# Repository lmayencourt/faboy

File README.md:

# faboy
arduboy clone for the fablab of Sion (CH)

## faboyBLE (V2)
The new version of the faboy is based on a nrf52822 module, an ARM cortex M0+ based processor with Bluetooth Smart. This will allow the possibility to change game wia BLE or UART and to have multiplayer games.  
### status

* PCB designed, ordered and mounted

### issues 
* cannot programm the nrf module...

## idea for v2 
  * NRF24l for a wireless communication
  * capacitive button
  * coin-cell battery / thin film battery 
  * different switch pattern
  * ARM processor 
  * solar cell
  * PCB usb connector 
  * battery monitoring with ADC

## issues 
  * bad usb connector (mini b instead of micro b !)
  * difficult to find a gnd test pad on the top 
  * battery operation crash after a small moment

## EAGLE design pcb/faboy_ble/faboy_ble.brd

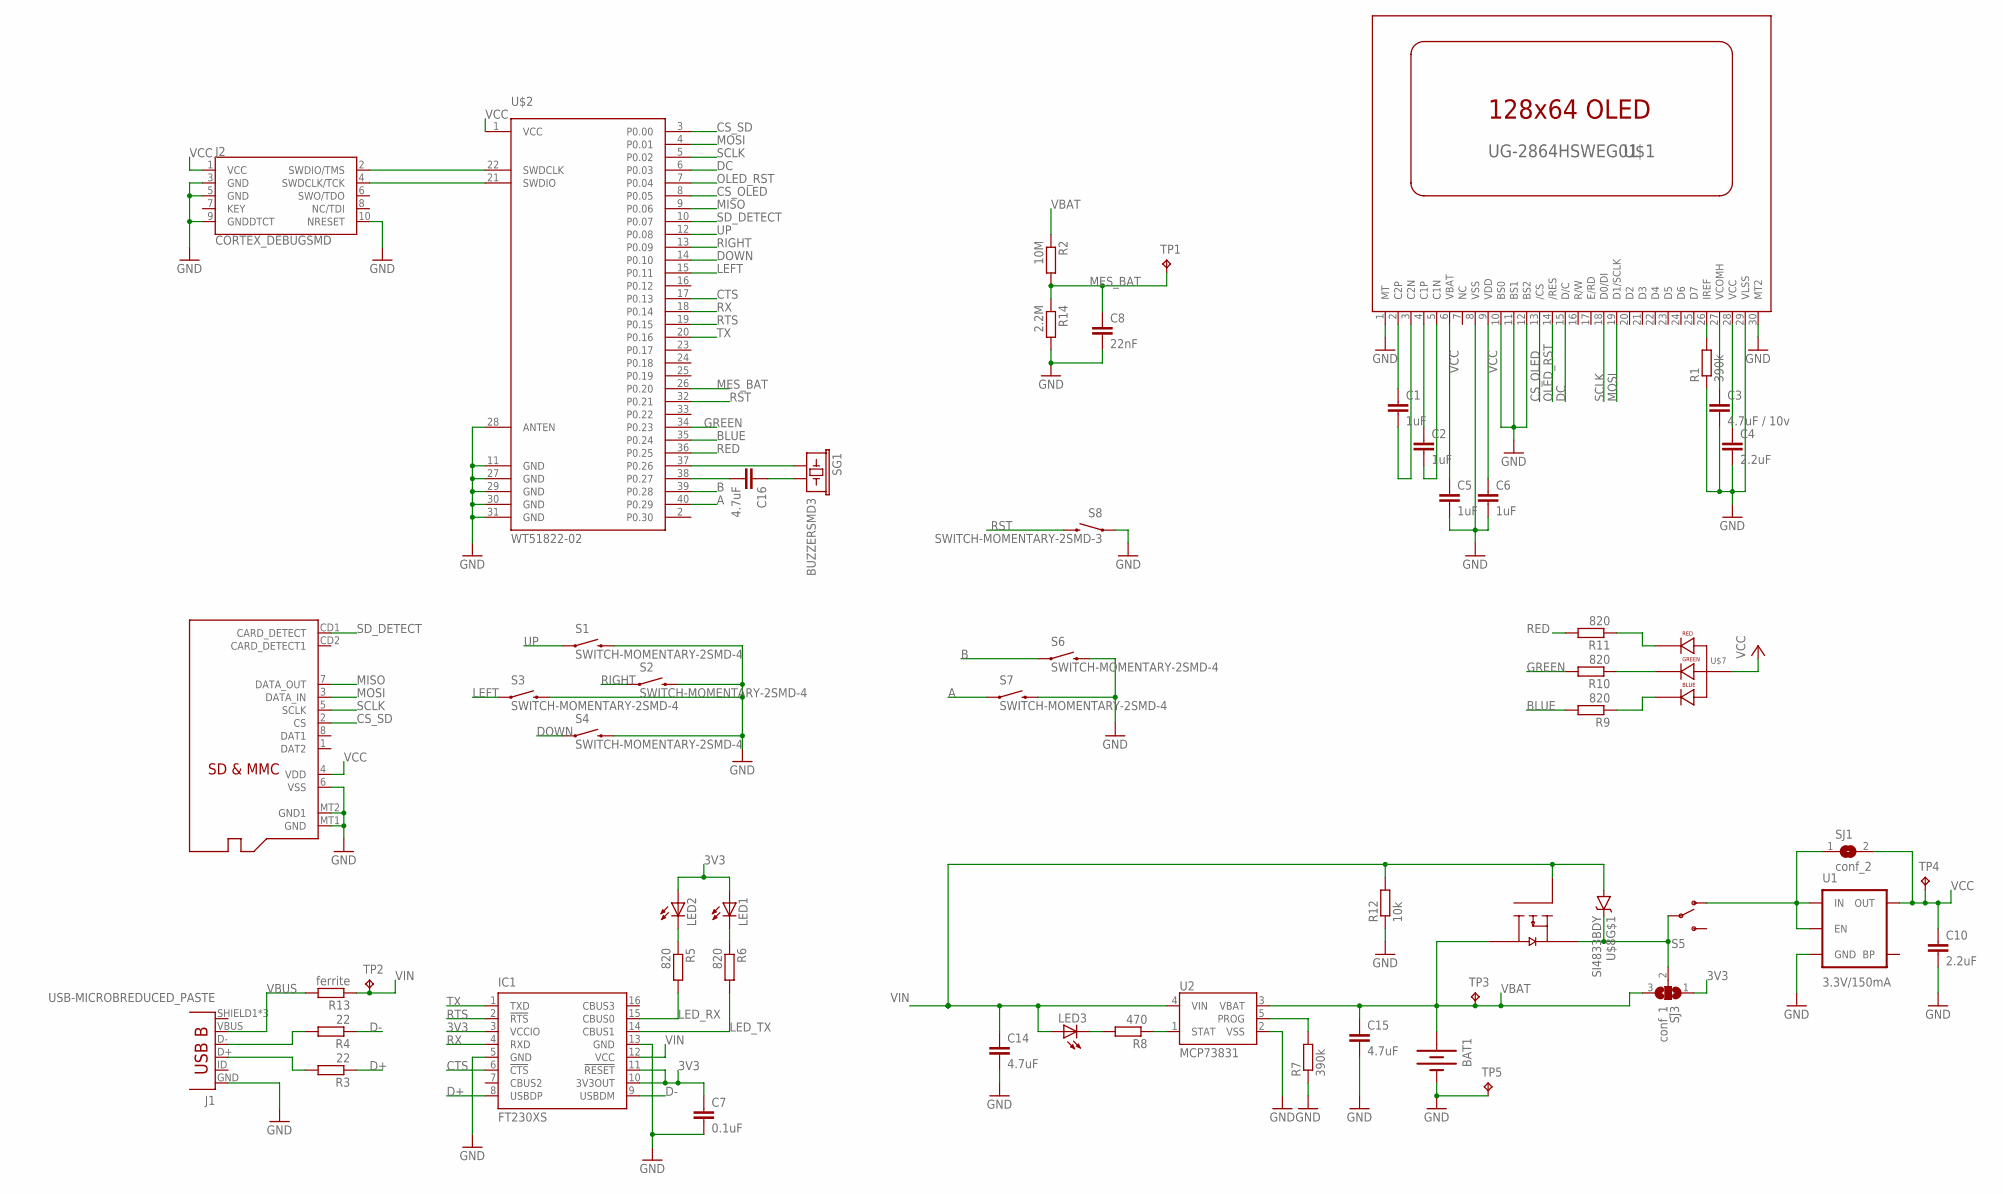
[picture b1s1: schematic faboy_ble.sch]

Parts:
BAT1: BATTERY20SMD; BATTCON_20MM
C1, C2, C5, C6: 1uF; C0805K
C3: 4.7uF / 10v; C0805K
C4, C10: 2.2uF; C0805K
C7: 0.1uF; C0805K
C8: 22nF; C0805K
C14, C15, C16: 4.7uF; C0805K
IC1: FT230XS; SSOP16
J1: USB-MICROBREDUCED_PASTE; USB-B-MICRO-SMD_V03_RED_PASTE
J2: CORTEX_DEBUGSMD; SAMTECH_FTSH-105-01
LED1, LED2, LED3: LEDSML0805; SML0805
R1, R7: 390k; R0805
R2: 10M; R0805
R3, R4: 22; R0805
R5, R6, R9, R10, R11: 820; R0805
R8: 470; R0805
R12: 10k; R0805
R13: ferrite; R0805
R14: 2.2M; R0805
S1, S2, S3, S4, S6, S7: SWITCH-MOMENTARY-2SMD-4; TACTILE_SWITCH_TALL
S5: SWITCH-SPDT-SMD-A; SWITCH-SPST-SMD-A
S8: SWITCH-MOMENTARY-2SMD-3; TACTILE_SWITCH_SMD-3
SG1: BUZZERSMD3; BUZZER-CMT1102
SJ1: conf_2; SJ
SJ3: conf_1; SJ_2
TP1, TP2, TP3, TP4, TP5: TPB1,27; B1,27
U1: 3.3V/150mA; SOT23-5
U2: MCP73831; SOT23-5
U$1: UG-2864HSWEG01; 1X30-0.7MM
U$2: WT51822-02; WT51822
U$7: LED-RGB-P-LCC-4; P-LCC-4-3
U$8: SI4833BDY; SO08
U$9: MICROSD

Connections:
3V3: C7.1, IC1.3 (VCCIO), IC1.10 (3V3OUT), IC1.11 (!RESET), LED1.A, LED2.A, SJ3.1
A: S7.A2 (1), U$2.40 (P0.29)
B: S6.A2 (1), U$2.39 (P0.28)
BLUE: R9.2, U$2.35 (P0.24)
CS_OLED: U$1.13 (/CS), U$2.8 (P0.05)
CS_SD: U$2.3 (P0.00), U$9.2 (CS)
CTS: IC1.6 (!CTS), U$2.17 (P0.13)
D+: IC1.8 (USBDP), R3.1
D-: IC1.9 (USBDM), R4.1
DC: U$1.15 (D/C), U$2.6 (P0.03)
DOWN: S4.A2 (1), U$2.14 (P0.10)
GND: BAT1.2 (-), C3.2, C4.2, C5.2, C6.2, C7.2, C8.2, C10.2, C14.2, C15.2, IC1.5 (GND), IC1.13 (GND), J1.GND, J2.3 (GND), J2.5 (GND), J2.9 (GNDDTCT), J2.10 (NRESET), R1.1, R7.1, R12.1, R14.2, S1.B2 (2), S2.B2 (2), S3.B2 (2), S4.B2 (2), S6.B2 (2), S7.B2 (2), S8.1, TP5.TP, U1.2 (GND), U2.2 (VSS), U$1.1 (MT), U$1.8 (VSS), U$1.10 (BS0), U$1.11 (BS1), U$1.12 (BS2), U$1.29 (VLSS), U$1.30 (MT2), U$2.11 (GND), U$2.27 (GND), U$2.28 (ANTEN), U$2.29 (GND), U$2.30 (GND), U$2.31 (GND)
GREEN: R10.2, U$2.34 (P0.23)
LED_RX: IC1.15 (CBUS0), R5.2
LED_TX: IC1.14 (CBUS1), R6.2
LEFT: S3.A2 (1), U$2.15 (P0.11)
MES_BAT: C8.1, R2.2, R14.1, TP1.TP, U$2.26 (P0.20)
MISO: U$2.9 (P0.06), U$9.7 (DATA_OUT)
MOSI: U$1.19 (D1/SCLK), U$2.4 (P0.01), U$9.3 (DATA_IN)
unnamed: C1.1, U$1.2 (C2P)
unnamed: C1.2, U$1.3 (C2N)
unnamed: C2.1, U$1.4 (C1P)
unnamed: C2.2, U$1.5 (C1N)
unnamed: R1.2, U$1.26 (IREF)
unnamed: R11.1, U$7.1 (RED_CATHODE)
unnamed: C3.1, U$1.27 (VCOMH)
unnamed: C4.1, U$1.28 (VCC)
unnamed: S5.1 (O), SJ1.1, U1.1 (IN), U1.3 (EN)
unnamed: C16.2, U$2.38 (P0.27)
unnamed: C16.1, SG1.2
unnamed: J1.D+, R3.2
unnamed: J1.D-, R4.2
unnamed: R8.1, U2.1 (STAT)
unnamed: LED3.C, R8.2
unnamed: R7.2, U2.5 (PROG)
unnamed: SG1.1, U$2.37 (P0.26)
unnamed: R10.1, U$7.4 (GREEN_CATHODE)
unnamed: LED2.C, R5.1
unnamed: R9.1, U$7.3 (BLUE_CATHODE)
unnamed: LED1.C, R6.1
unnamed: S5.2, SJ3.2, U$8.3 (S2), U$8.7 (C), U$8.8 (C)
OLED_RST: U$1.14 (/RES), U$2.7 (P0.04)
RED: R11.2, U$2.36 (P0.25)
RIGHT: S2.A2 (1), U$2.13 (P0.09)
RST: S8.4 (2), U$2.32 (P0.21)
RTS: IC1.2 (!RTS), U$2.19 (P0.15)
RX: IC1.4 (RXD), U$2.18 (P0.14)
SCLK: U$1.18 (D0/DI), U$2.5 (P0.02), U$9.5 (SCLK)
SD_DETECT: U$2.10 (P0.07), U$9.CD1 (CARD_DETECT)
SWDCLK: J2.4 (SWDCLK/TCK), U$2.21 (SWDIO)
SWDIO: J2.2 (SWDIO/TMS), U$2.22 (SWDCLK)
TX: IC1.1 (TXD), U$2.20 (P0.16)
UP: S1.A2 (1), U$2.12 (P0.08)
VBAT: BAT1.3 (+), C15.1, R2.1, SJ3.3, TP3.TP, U2.3 (VBAT), U$8.5 (D2), U$8.6 (D2)
VBUS: J1.VBUS, R13.2
VCC: C5.1, C6.1, C10.1, J2.1 (VCC), SJ1.2, TP4.TP, U1.5 (OUT), U$1.6 (VBAT), U$1.9 (VDD), U$2.1 (VCC), U$7.2 (ANODE), U$9.4 (VDD)
VIN: C14.1, IC1.12 (VCC), LED3.A, R12.2, R13.1, TP2.TP, U2.4 (VIN), U$8.1 (A), U$8.2 (A), U$8.4 (G2)
VSS: U$9.6 (VSS), U$9.MT1 (GND), U$9.MT2 (GND1)

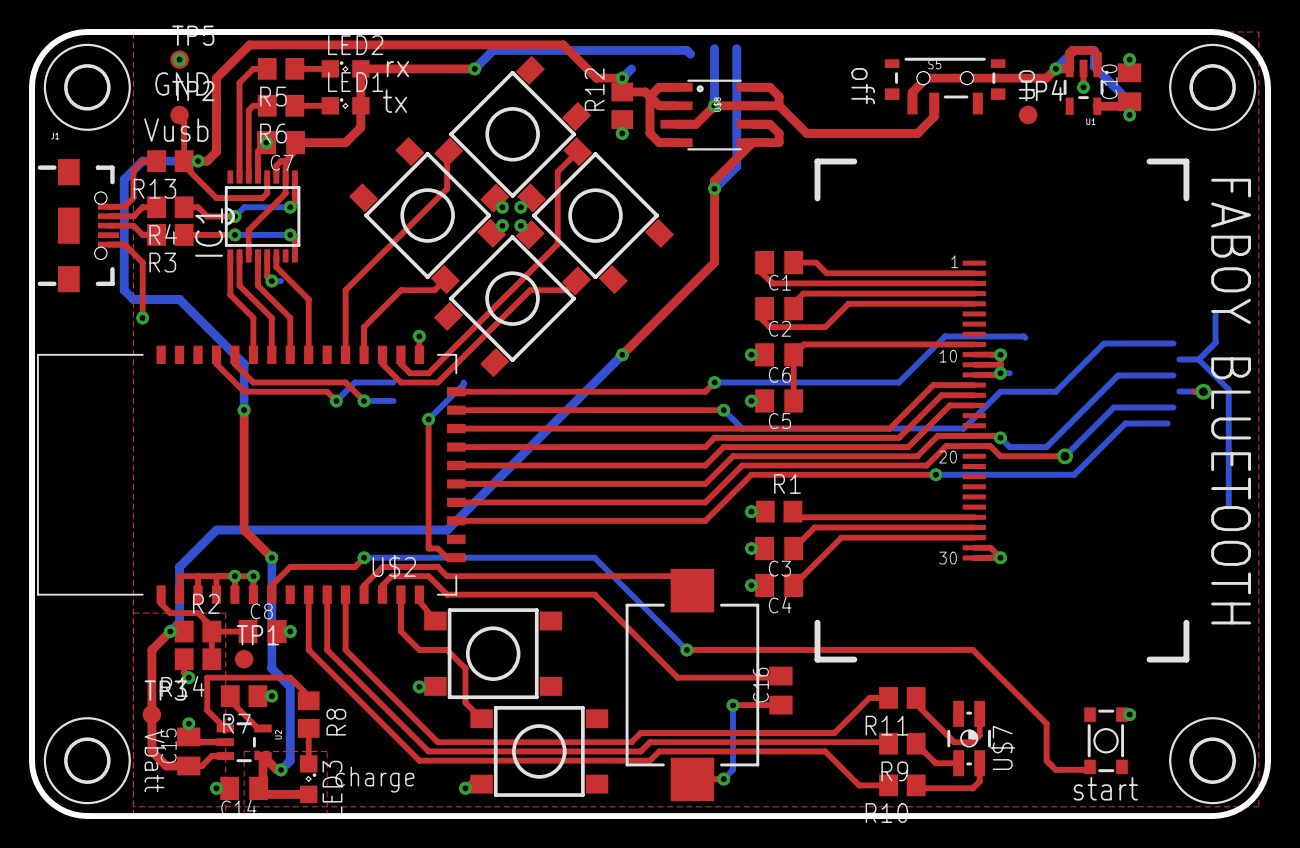
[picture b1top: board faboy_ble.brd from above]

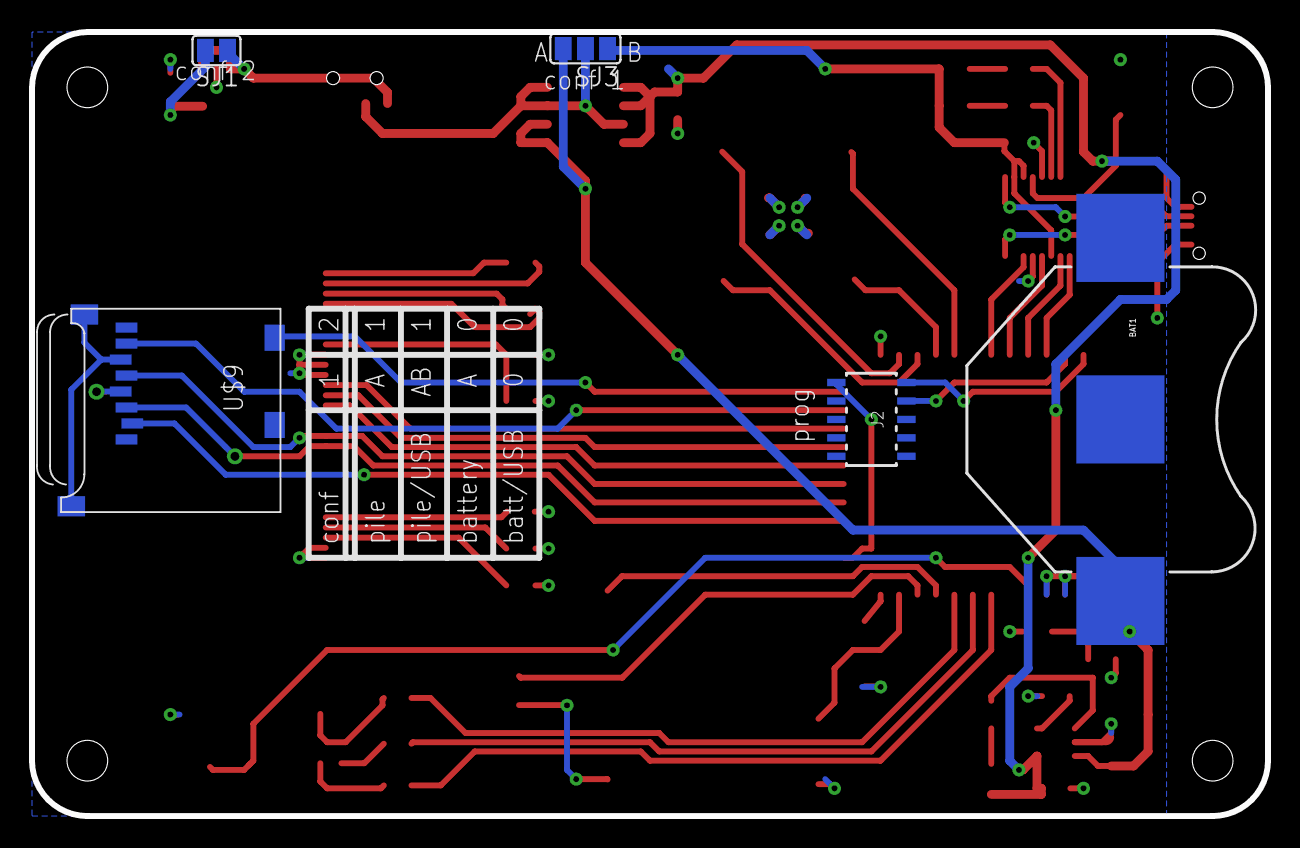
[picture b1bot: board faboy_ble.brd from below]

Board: 2 copper layers, 85.1 x 54.0 mm, 60 parts (5 on the bottom side), 58 nets.

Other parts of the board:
U$3, U$4, U$6: 2,8
U$5: gnd; 2,8

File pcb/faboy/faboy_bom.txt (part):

Partlist exported from /home/louis/eagle/faboy/pcb/faboy/faboy.sch at 01.12.16 16:03

Part Value                           Device                          Package                       Description                                                                             PROD_ID    VALUE
BAT1                                 BATTERY20SMD                    BATTCON_20MM                  Battery Holders                                                                                         
C1   1uF                             C-EUC0805K                      C0805K                        CAPACITOR, European symbol                                                                              
C2   1uF                             C-EUC0805K                      C0805K                        CAPACITOR, European symbol                                                                              
C3   4.7uF / 10v                     C-EUC0805K                      C0805K                        CAPACITOR, European symbol                                                                              
C4   2.2uF                           C-EUC0805K                      C0805K                        CAPACITOR, European symbol                                                                              
C5   1uF                             C-EUC0805K                      C0805K                        CAPACITOR, European symbol                                                                              
C6   1uF                             C-EUC0805K                      C0805K                        CAPACITOR, European symbol                                                                              
C7   1uF                             C-EUC0805K                      C0805K                        CAPACITOR, European symbol                                                                              
C8   1uF                             C-EUC0805K                      C0805K                        CAPACITOR, European symbol                                                                              
C9   0.1uF                           C-EUC0805K                      C0805K                        CAPACITOR, European symbol                                                                              
C10  1uF                             C-EUC0805K                      C0805K                        CAPACITOR, European symbol                                                                              
C11  0.47uF                          C-EUC0805K                      C0805K                        CAPACITOR, European symbol                                                                              
C12  2.2uF                           C-EUC0805K                      C0805K                        CAPACITOR, European symbol                                                                              
C13  2.2uF                           C-EUC0805K                      C0805K                        CAPACITOR, European symbol                                                                              
C14  4.7uF                           C-EUC0805K                      C0805K                        CAPACITOR, European symbol                                                                              
C15  4.7uF                           C-EUC0805K                      C0805K                        CAPACITOR, European symbol                                                                              
C16  4.7uF                           C-EUC0805K                      C0805K                        CAPACITOR, European symbol                                                                              
F1   500mA                           PTCFUSE-1812                    1812                          PTC fuses, resettable thermistors                                                                       
J1   USB-MICROBREDUCED_PASTE         USB-MICROBREDUCED_PASTE         USB-B-MICRO-SMD_V03_RED_PASTE RED_PASTE version has 70% paste area under D+ D- USBID pins for applications            CONN-11752      
J2                                   M06SMD-FEMALE-V2                1X06-SMD-FEMALE-V2            Header 6                                                                                CONN-09668      
LED1                                 LEDSML0805                      SML0805                       LED                                                                                                     
LED2                                 LEDSML0805                      SML0805                       LED                                                                                                     
LED3                                 LEDSML0805                      SML0805                       LED                                                                                                     
R1   390k                            R-EU_R0805                      R0805                         RESISTOR, European symbol                                                                               
R2   10k                             R-EU_R0805                      R0805                         RESISTOR, European symbol                                                                               
R3   22                              R-EU_R0805                      R0805                         RESISTOR, European symbol                                                                               
R4   22                              R-EU_R0805                      R0805                         RESISTOR, European symbol                                                                               
R5   820                             R-EU_R0805                      R0805                         RESISTOR, European symbol                                                                               
R6   820                             R-EU_R0805                      R0805                         RESISTOR, European symbol                                                                               
R7   390k                            R-EU_R0805                      R0805                         RESISTOR, European symbol                                                                               
R8   470                             R-EU_R0805                      R0805                         RESISTOR, European symbol                                                                               
R9   820                             R-EU_R0805                      R0805                         RESISTOR, European symbol                                                                               
R10  820                             R-EU_R0805                      R0805                         RESISTOR, European symbol                                                                               
R11  820                             R-EU_R0805                      R0805                         RESISTOR, European symbol                                                                               
R12  10k                             R-EU_R0805                      R0805                         RESISTOR, European symbol                                                                               
S1   SWITCH-MOMENTARY-2SMD-REDUNDANT SWITCH-MOMENTARY-2SMD-REDUNDANT TACTILE-SWITCH-SMD            Various NO switches- pushbuttons, reed, etc                                             SWCH-08247      
S2   SWITCH-MOMENTARY-2SMD-REDUNDANT SWITCH-MOMENTARY-2SMD-REDUNDANT TACTILE-SWITCH-SMD            Various NO switches- pushbuttons, reed, etc                                             SWCH-08247      
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
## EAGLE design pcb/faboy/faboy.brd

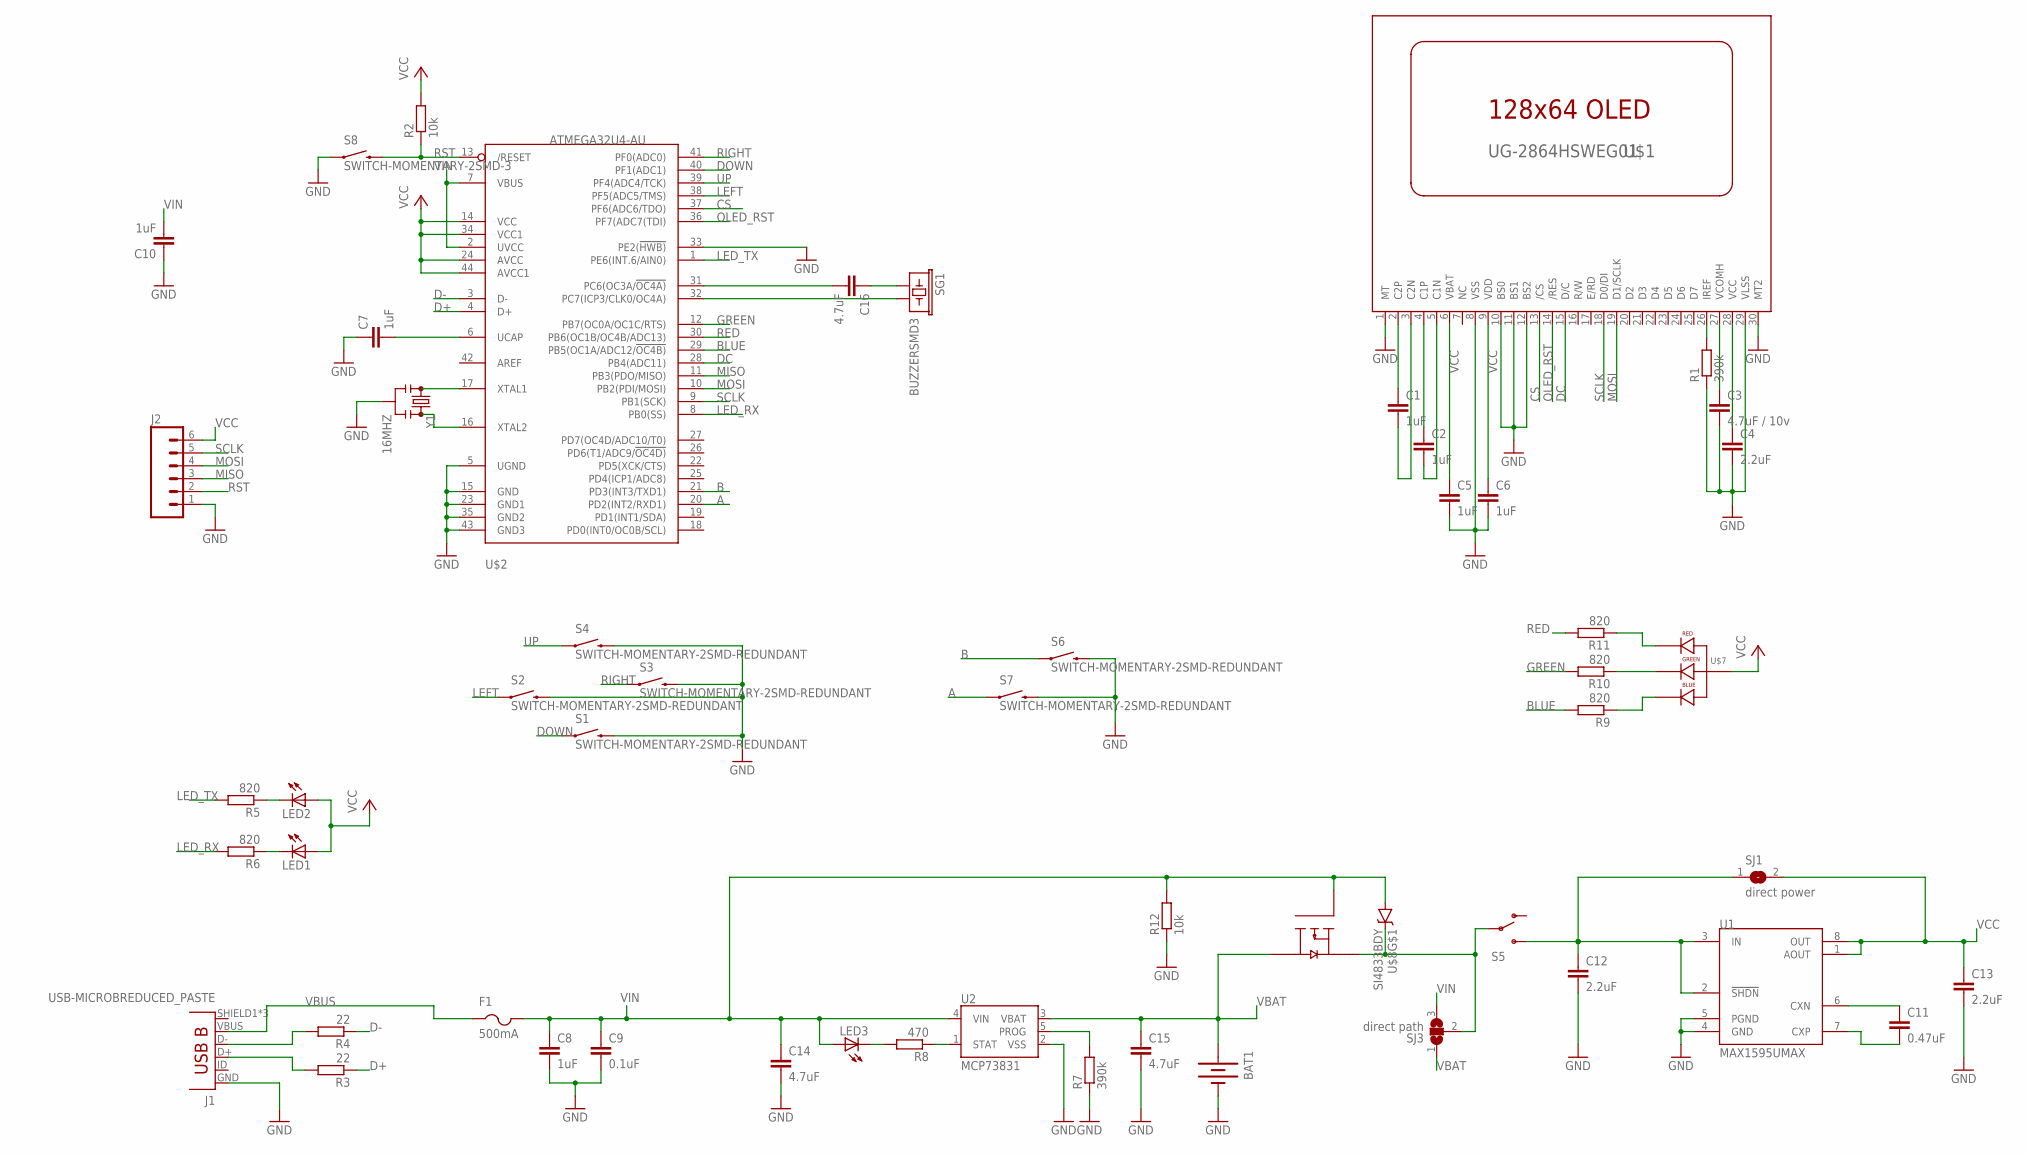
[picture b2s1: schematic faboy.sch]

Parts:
BAT1: BATTERY20SMD; BATTCON_20MM
C1, C2, C5, C6, C7, C8, C10: 1uF; C0805K
C3: 4.7uF / 10v; C0805K
C4, C12, C13: 2.2uF; C0805K
C9: 0.1uF; C0805K
C11: 0.47uF; C0805K
C14, C15, C16: 4.7uF; C0805K
F1: 500mA; 1812
J1: USB-MICROBREDUCED_PASTE; USB-B-MICRO-SMD_V03_RED_PASTE
J2: M06SMD-FEMALE-V2; 1X06-SMD-FEMALE-V2
LED1, LED2, LED3: LEDSML0805; SML0805
R1, R7: 390k; R0805
R2, R12: 10k; R0805
R3, R4: 22; R0805
R5, R6, R9, R10, R11: 820; R0805
R8: 470; R0805
S1, S2, S3, S4, S6, S7: SWITCH-MOMENTARY-2SMD-REDUNDANT; TACTILE-SWITCH-SMD
S5: SWITCH-SPDT-SMD-A; SWITCH-SPST-SMD-A
S8: SWITCH-MOMENTARY-2SMD-3; TACTILE_SWITCH_SMD-3
SG1: BUZZERSMD3; BUZZER-CMT1102
SJ1: direct power; SJ
SJ3: direct path; SJ_2
U1: MAX1595UMAX; UMAX8
U2: MCP73831; SOT23-5
U$1: UG-2864HSWEG01; 1X30-0.7MM
U$2: ATMEGA32U4-AU; TQFP44
U$7: LED-RGB-P-LCC-4; P-LCC-4-3
U$8: SI4833BDY; SO08
Y1: 16MHZ; RESONATOR-SMD

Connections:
A: S7.1, S7.2 (1), U$2.20 (PD2(INT2/RXD1))
B: S6.1, S6.2 (1), U$2.21 (PD3(INT3/TXD1))
BLUE: R9.2, U$2.29 (PB5(OC1A/ADC12/!OC4B))
CS: U$1.13 (/CS), U$2.37 (PF6(ADC6/TDO))
D+: R3.1, U$2.4 (D+)
D-: R4.1, U$2.3 (D-)
DC: U$1.15 (D/C), U$2.28 (PB4(ADC11))
DOWN: S1.1, S1.2 (1), U$2.40 (PF1(ADC1))
GND: BAT1.2 (-), C3.2, C4.2, C5.2, C6.2, C7.1, C8.2, C9.2, C10.1, C12.2, C13.2, C14.2, C15.2, J1.GND, J2.1, R1.1, R7.1, R12.1, S1.3 (2), S1.4 (2), S2.3 (2), S2.4 (2), S3.3 (2), S3.4 (2), S4.3 (2), S4.4 (2), S6.3 (2), S6.4 (2), S7.3 (2), S7.4 (2), S8.1, U1.4 (GND), U1.5 (PGND), U2.2 (VSS), U$1.1 (MT), U$1.8 (VSS), U$1.10 (BS0), U$1.11 (BS1), U$1.12 (BS2), U$1.29 (VLSS), U$1.30 (MT2), U$2.5 (UGND), U$2.15 (GND), U$2.23 (GND1), U$2.33 (PE2(!HWB)), U$2.35 (GND2), U$2.43 (GND3), Y1.2
GREEN: R10.2, U$2.12 (PB7(OC0A/OC1C/RTS))
LED_RX: R6.2, U$2.8 (PB0(SS))
LED_TX: R5.2, U$2.1 (PE6(INT.6/AIN0))
LEFT: S2.1, S2.2 (1), U$2.38 (PF5(ADC5/TMS))
MISO: J2.3, U$2.11 (PB3(PDO/MISO))
MOSI: J2.4, U$1.19 (D1/SCLK), U$2.10 (PB2(PDI/MOSI))
unnamed: C1.1, U$1.2 (C2P)
unnamed: C1.2, U$1.3 (C2N)
unnamed: C2.1, U$1.4 (C1P)
unnamed: C2.2, U$1.5 (C1N)
unnamed: R1.2, U$1.26 (IREF)
unnamed: R11.1, U$7.1 (RED_CATHODE)
unnamed: C3.1, U$1.27 (VCOMH)
unnamed: C4.1, U$1.28 (VCC)
unnamed: C7.2, U$2.6 (UCAP)
unnamed: C12.1, S5.3 (S), SJ1.1, U1.2 (!SHDN), U1.3 (IN)
unnamed: U$2.17 (XTAL1), Y1.1
unnamed: J1.D+, R3.2
unnamed: J1.D-, R4.2
unnamed: U$2.16 (XTAL2), Y1.3
unnamed: C11.1, U1.6 (CXN)
unnamed: C11.2, U1.7 (CXP)
unnamed: R8.1, U2.1 (STAT)
unnamed: LED3.C, R8.2
unnamed: R7.2, U2.5 (PROG)
unnamed: C16.2, U$2.31 (PC6(OC3A/!OC4A))
unnamed: C16.1, SG1.1
unnamed: R10.1, U$7.4 (GREEN_CATHODE)
unnamed: LED2.C, R5.1
unnamed: R9.1, U$7.3 (BLUE_CATHODE)
unnamed: LED1.C, R6.1
unnamed: SG1.2, U$2.32 (PC7(ICP3/CLK0/OC4A))
unnamed: S5.2, SJ3.2, U$8.3 (S2), U$8.7 (C), U$8.8 (C)
OLED_RST: U$1.14 (/RES), U$2.36 (PF7(ADC7(TDI))
RED: R11.2, U$2.30 (PB6(OC1B/OC4B/ADC13))
RIGHT: S3.1, S3.2 (1), U$2.41 (PF0(ADC0))
RST: J2.2, R2.1, S8.4 (2), U$2.13 (/RESET)
SCLK: J2.5, U$1.18 (D0/DI), U$2.9 (PB1(SCK))
UP: S4.1, S4.2 (1), U$2.39 (PF4(ADC4/TCK))
VBAT: BAT1.1 (+), C15.1, SJ3.1, U2.3 (VBAT), U$8.5 (D2), U$8.6 (D2)
VBUS: F1.1, J1.VBUS
VCC: C5.1, C6.1, C13.1, J2.6, LED1.A, LED2.A, R2.2, SJ1.2, U1.1 (AOUT), U1.8 (OUT), U$1.6 (VBAT), U$1.9 (VDD), U$2.14 (VCC), U$2.24 (AVCC), U$2.34 (VCC1), U$2.44 (AVCC1), U$7.2 (ANODE)
VIN: C8.1, C9.1, C10.2, C14.1, F1.2, LED3.A, R12.2, SJ3.3, U2.4 (VIN), U$2.2 (UVCC), U$2.7 (VBUS), U$8.1 (A), U$8.2 (A), U$8.4 (G2)

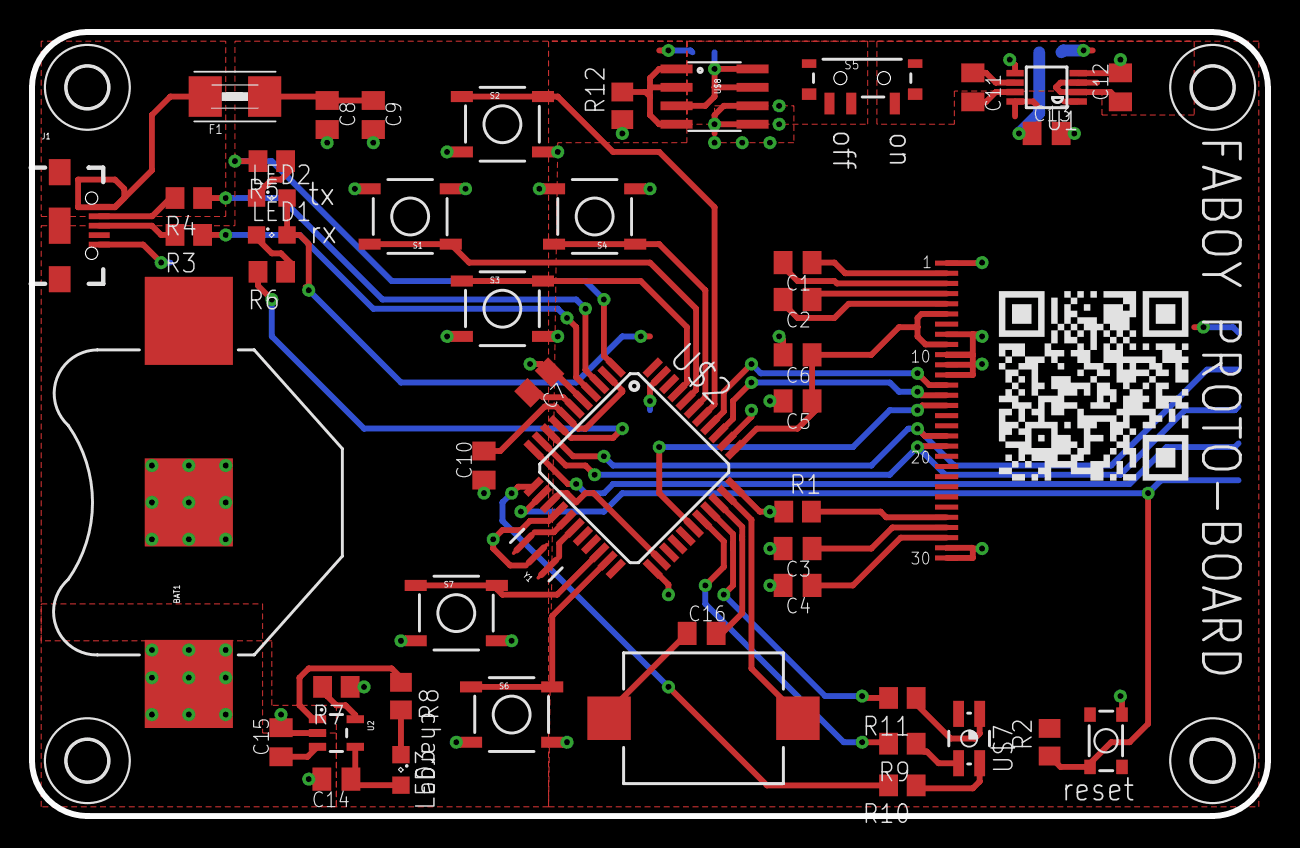
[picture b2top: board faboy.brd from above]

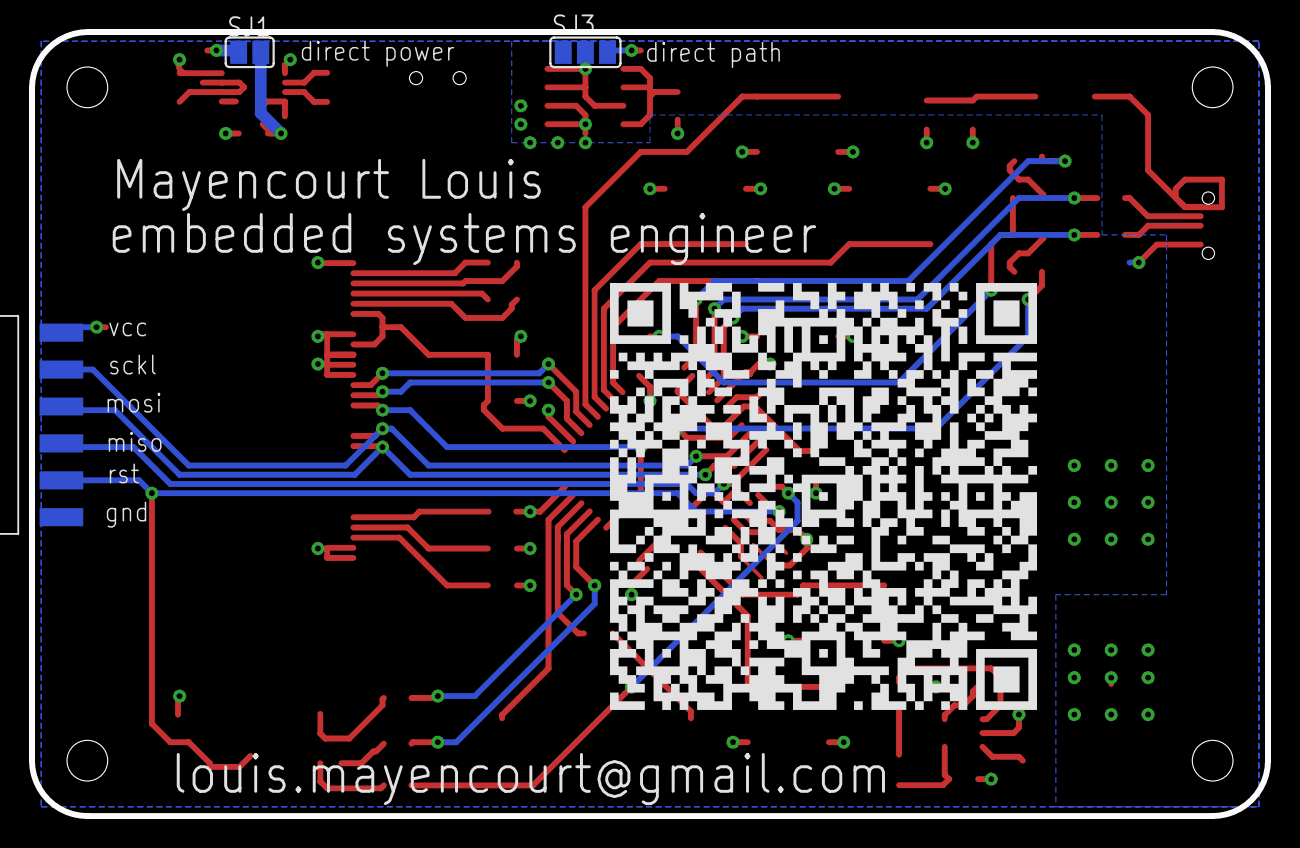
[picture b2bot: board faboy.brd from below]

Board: 2 copper layers, 85.1 x 54.0 mm, 57 parts (3 on the bottom side), 52 nets.

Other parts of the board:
U$3, U$4, U$6: 2,8
U$5: gnd; 2,8

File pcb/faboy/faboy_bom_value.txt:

Partlist exported from /home/louis/eagle/faboy/pcb/faboy/faboy.sch at 01.12.16 16:02

Qty Value                           Device                          Package                       Parts                       Description                                                                             PROD_ID    VALUE
1                                   BATTERY20SMD                    BATTCON_20MM                  BAT1                        Battery Holders                                                                                         
3                                   LEDSML0805                      SML0805                       LED1, LED2, LED3            LED                                                                                                     
1                                   M06SMD-FEMALE-V2                1X06-SMD-FEMALE-V2            J2                          Header 6                                                                                CONN-09668      
1                                   SWITCH-SPDT-SMD-A               SWITCH-SPST-SMD-A             S5                          SPDT Switch                                                                             SWCH-10651      
1   0.1uF                           C-EUC0805K                      C0805K                        C9                          CAPACITOR, European symbol                                                                              
1   0.47uF                          C-EUC0805K                      C0805K                        C11                         CAPACITOR, European symbol                                                                              
2   10k                             R-EU_R0805                      R0805                         R2, R12                     RESISTOR, European symbol                                                                               
1   16MHZ                           RESONATOR16MHZ                  RESONATOR-SMD                 Y1                          Resonator                                                                               XTAL-08900 16MHZ
7   1uF                             C-EUC0805K                      C0805K                        C1, C2, C5, C6, C7, C8, C10 CAPACITOR, European symbol                                                                              
3   2.2uF                           C-EUC0805K                      C0805K                        C4, C12, C13                CAPACITOR, European symbol                                                                              
2   22                              R-EU_R0805                      R0805                         R3, R4                      RESISTOR, European symbol                                                                               
2   390k                            R-EU_R0805                      R0805                         R1, R7                      RESISTOR, European symbol                                                                               
3   4.7uF                           C-EUC0805K                      C0805K                        C14, C15, C16               CAPACITOR, European symbol                                                                              
1   4.7uF / 10v                     C-EUC0805K                      C0805K                        C3                          CAPACITOR, European symbol                                                                              
1   470                             R-EU_R0805                      R0805                         R8                          RESISTOR, European symbol                                                                               
1   500mA                           PTCFUSE-1812                    1812                          F1                          PTC fuses, resettable thermistors                                                                       
5   820                             R-EU_R0805                      R0805                         R5, R6, R9, R10, R11        RESISTOR, European symbol                                                                               
1   ATMEGA32U4-AU                   ATMEGA32U4-AU                   TQFP44                        U$2                         http://www.ladyada.net/library/eagle                                                                    
1   BUZZERSMD3                      BUZZERSMD3                      BUZZER-CMT1102                SG1                         Buzzer 12mm                                                                                             
1   LED-RGB-P-LCC-4                 LED-RGB-P-LCC-4                 P-LCC-4-3                     U$7                                                                                                                                 
1   MAX1595UMAX                     MAX1595UMAX                     UMAX8                         U1                          max1595 buck/boost dcdc 3.3v output                                                                     
1   MCP73831                        MCP73831                        SOT23-5                       U2                          Miniature single cell, fully integrated Li-Ion, Li-polymer charge management controller IC-09995        
1   SI4833BDY                       SI4833BDY                       SO08                          U$8                                                                                                                                 
1   SWITCH-MOMENTARY-2SMD-3         SWITCH-MOMENTARY-2SMD-3         TACTILE_SWITCH_SMD-3          S8                          Various NO switches- pushbuttons, reed, etc                                                             
6   SWITCH-MOMENTARY-2SMD-REDUNDANT SWITCH-MOMENTARY-2SMD-REDUNDANT TACTILE-SWITCH-SMD            S1, S2, S3, S4, S6, S7      Various NO switches- pushbuttons, reed, etc                                             SWCH-08247      
1   UG-2864HSWEG01                  UG-2864HSWEG01                  1X30-0.7MM                    U$1                         UG-2864HSWEG01 OLED display                                                                             
1   USB-MICROBREDUCED_PASTE         USB-MICROBREDUCED_PASTE         USB-B-MICRO-SMD_V03_RED_PASTE J1                          RED_PASTE version has 70% paste area under D+ D- USBID pins for applications            CONN-11752      
1   direct path                     SJ2W                            SJ_2                          SJ3                         SMD solder JUMPER                                                                                       
1   direct power                    SJ                              SJ                            SJ1                         SMD solder JUMPER

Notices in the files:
parts and their libraries:
SparkFun-Electromechanical: Licensing: Creative Commons ShareAlike 4.0 International - https://creativecommons.org/licenses/by-sa/4.0
